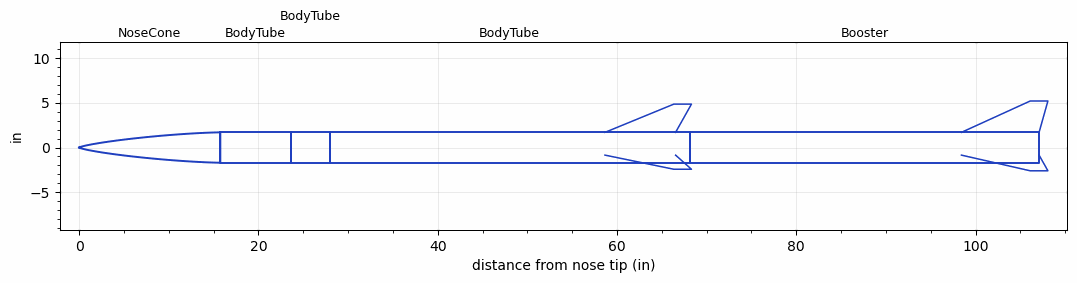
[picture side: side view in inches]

<RASAeroDocument>
 <FileVersion>2</FileVersion>
 <RocketDesign>
  <NoseCone>
   <Length>15.748</Length>
   <Diameter>3.3858</Diameter>
   <Shape>Von Karman Ogive</Shape>
   <Location>0</Location>
  </NoseCone>
  <BodyTube>
   <Length>7.874</Length>
   <Diameter>3.3858</Diameter>
   <Location>15.748</Location>
  </BodyTube>
  <BodyTube>
   <Length>4.3307</Length>
   <Diameter>3.3858</Diameter>
   <Location>23.622</Location>
  </BodyTube>
  <BodyTube>
   <Length>40.1574</Length>
   <Diameter>3.3858</Diameter>
   <Location>27.9527</Location>
   <Fin>
    <Count>3</Count>
    <Chord>7.874</Chord>
    <Span>3.1496</Span>
    <SweepDistance>7.6772</SweepDistance>
    <TipChord>1.9685</TipChord>
    <Thickness>0.125</Thickness>
    <Location>9.4488</Location>
    <AirfoilSection>Rounded</AirfoilSection>
   </Fin>
  </BodyTube>
  <Booster>
   <Length>38.9763</Length>
   <Diameter>3.3858</Diameter>
   <InsideDiameter>3.3858</InsideDiameter>
   <Location>68.1101</Location>
   <ShoulderLength>0</ShoulderLength>
   <Fin>
    <Count>3</Count>
    <Chord>8.6614</Chord>
    <Span>3.5</Span>
    <SweepDistance>7.6772</SweepDistance>
    <TipChord>1.9685</TipChord>
    <Thickness>0.125</Thickness>
    <Location>8.6614</Location>
    <AirfoilSection>Rounded</AirfoilSection>
   </Fin>
  </Booster>
  <Surface>Smooth Paint</Surface>
  <ModifiedBarrowman>False</ModifiedBarrowman>
  <Turbulence>False</Turbulence>
  <UseBooster1>True</UseBooster1>
  <UseBooster2>False</UseBooster2>
 </RocketDesign>
 <LaunchSite>
  <Altitude>1249</Altitude>
  <Pressure>0</Pressure>
  <RodAngle>0</RodAngle>
  <RodLength>39.37</RodLength>
  <Temperature>92</Temperature>
  <WindSpeed>4.47</WindSpeed>
 </LaunchSite>
 <Recovery>
  <Altitude1>656.168</Altitude1>
  <Altitude2>656.168</Altitude2>
  <DeviceType1>Parachute</DeviceType1>
  <DeviceType2>Parachute</DeviceType2>
  <Event1>True</Event1>
  <Event2>True</Event2>
  <Size1>39.9999</Size1>
  <Size2>15</Size2>
  <EventType1>Altitude</EventType1>
  <EventType2>Apogee</EventType2>
  <CD1>0.8</CD1>
  <CD2>0</CD2>
 </Recovery>
 <SimulationList>
  <Simulation>
   <SustainerEngine>M1315W  (AT)</SustainerEngine>
   <SustainerLaunchWt>18.1407</SustainerLaunchWt>
   <SustainerCG>46.3655</SustainerCG>
   <SustainerIgnitionDelay>20</SustainerIgnitionDelay>
   <Booster1Engine>M1315W  (AT)</Booster1Engine>
   <Booster1LaunchWt>34.8171</Booster1LaunchWt>
   <Booster1SeparationDelay>1</Booster1SeparationDelay>
   <Booster1IgnitionDelay>0</Booster1IgnitionDelay>
   <Booster1CG>67.1348</Booster1CG>
   <IncludeBooster1>True</IncludeBooster1>
   <Booster2Delay>0</Booster2Delay>
   <IncludeBooster2>False</IncludeBooster2>
  </Simulation>
  <Simulation>
   <SustainerLaunchWt>13.9674</SustainerLaunchWt>
   <SustainerCG>48.2517</SustainerCG>
   <SustainerIgnitionDelay>16</SustainerIgnitionDelay>
   <Booster1LaunchWt>26.4704</Booster1LaunchWt>
   <Booster1SeparationDelay>1</Booster1SeparationDelay>
   <Booster1IgnitionDelay>0</Booster1IgnitionDelay>
   <Booster1CG>69.5292</Booster1CG>
   <IncludeBooster1>True</IncludeBooster1>
   <Booster2Delay>0</Booster2Delay>
   <IncludeBooster2>False</IncludeBooster2>
  </Simulation>
  <Simulation>
   <SustainerEngine>K780R  (AT)</SustainerEngine>
   <SustainerLaunchWt>12.1653</SustainerLaunchWt>
   <SustainerCG>46.5702</SustainerCG>
   <SustainerIgnitionDelay>4</SustainerIgnitionDelay>
   <Booster1Engine>K780R  (AT)</Booster1Engine>
   <Booster1LaunchWt>22.8663</Booster1LaunchWt>
   <Booster1SeparationDelay>1</Booster1SeparationDelay>
   <Booster1IgnitionDelay>0</Booster1IgnitionDelay>
   <Booster1CG>68.0221</Booster1CG>
   <IncludeBooster1>True</IncludeBooster1>
   <Booster2Delay>0</Booster2Delay>
   <IncludeBooster2>False</IncludeBooster2>
  </Simulation>
  <Simulation>
   <SustainerEngine>M650W  (AT)</SustainerEngine>
   <SustainerLaunchWt>16.9948</SustainerLaunchWt>
   <SustainerCG>45.9625</SustainerCG>
   <SustainerIgnitionDelay>8</SustainerIgnitionDelay>
   <Booster1LaunchWt>29.3254</Booster1LaunchWt>
   <Booster1SeparationDelay>1</Booster1SeparationDelay>
   <Booster1IgnitionDelay>0</Booster1IgnitionDelay>
   <Booster1CG>65.6077</Booster1CG>
   <IncludeBooster1>True</IncludeBooster1>
   <Booster2Delay>0</Booster2Delay>
   <IncludeBooster2>False</IncludeBooster2>
  </Simulation>
  <Simulation>
   <SustainerEngine>L2200G  (AT)</SustainerEngine>
   <SustainerLaunchWt>16.1702</SustainerLaunchWt>
   <SustainerCG>46.9633</SustainerCG>
   <SustainerIgnitionDelay>6</SustainerIgnitionDelay>
   <Booster1Engine>L2200G  (AT)</Booster1Engine>
   <Booster1LaunchWt>30.8762</Booster1LaunchWt>
   <Booster1SeparationDelay>1</Booster1SeparationDelay>
   <Booster1IgnitionDelay>0</Booster1IgnitionDelay>
   <Booster1CG>67.9244</Booster1CG>
   <IncludeBooster1>True</IncludeBooster1>
   <Booster2Delay>0</Booster2Delay>
   <IncludeBooster2>False</IncludeBooster2>
  </Simulation>
  <Simulation>
   <SustainerEngine>L2200G  (AT)</SustainerEngine>
   <SustainerLaunchWt>16.17</SustainerLaunchWt>
   <SustainerNozzleDiameter>0.685</SustainerNozzleDiameter>
   <SustainerCG>46.96</SustainerCG>
   <SustainerIgnitionDelay>6</SustainerIgnitionDelay>
   <Booster1Engine>K560W  (AT)</Booster1Engine>
   <Booster1LaunchWt>26.38</Booster1LaunchWt>
   <Booster1SeparationDelay>1</Booster1SeparationDelay>
   <Booster1IgnitionDelay>0</Booster1IgnitionDelay>
   <Booster1CG>64.94</Booster1CG>
   <Booster1NozzleDiameter>0.485</Booster1NozzleDiameter>
   <IncludeBooster1>True</IncludeBooster1>
   <Booster2Delay>0</Booster2Delay>
   <IncludeBooster2>False</IncludeBooster2>
   <TimetoApogee>47.15914</TimetoApogee>
   <MaxAltitude>31944.56</MaxAltitude>
   <MaxVelocity>2568.237</MaxVelocity>
  </Simulation>
 </SimulationList>
</RASAeroDocument>
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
